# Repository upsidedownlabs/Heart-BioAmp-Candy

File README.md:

# Heart BioAmp Candy

[-white)](https://store.upsidedownlabs.tech/product/heart-bioamp-candy/)

Heart BioAmp Candy is a candy-sized sensor for recording ECG signals easily. It is perfect for students and researchers as it offers reliable and accurate ECG recordings, making heart monitoring accessible and convenient for educational and research purposes.

## Specifications

|Specs |      |
| ---- | ---- |
| Input Voltage | 2.7 V - 5 V |
| Fixed Gain | x2157 |
| Bandpass filter | 0.5 - 34 Hz |
| Compatible hardware | Any development board with an ADC (Arduino UNO R3/R4, Arduino Nano, Adafruit QtPy, STM32 Blue Pill, BeagleBone Black, Raspberry Pi Pico, to name just a few) or any standalone ADC of your choice |
| Biopotentials | ECG |
| No. of channels | 1 |
| Electrodes | 3 (Positive, Negative, and Reference) |
| Dimensions | 3.5 x 1.5 cm |
| Open-source | hardware + software |

## Hardware

Heart BioAmp Candy has been created using KiCad and all the design files can be found under [hardware](hardware/) folder, including [Interactive BOM](hardware/bom) file. Images below shows a quick overview of the hardware design.

## License

CERN Open Hardware License Version 2 - Strongly Reciprocal ([CERN-OHL-S-2.0](https://spdx.org/licenses/CERN-OHL-S-2.0.html)).

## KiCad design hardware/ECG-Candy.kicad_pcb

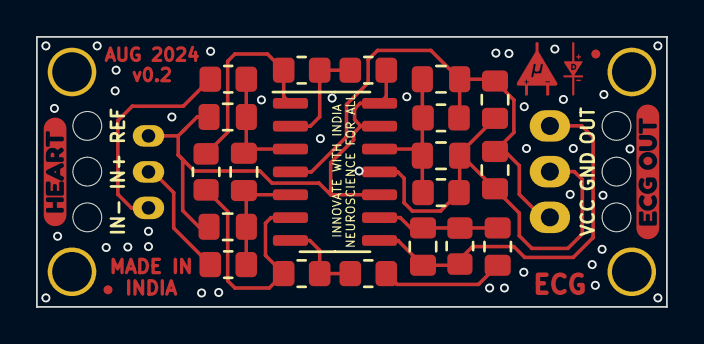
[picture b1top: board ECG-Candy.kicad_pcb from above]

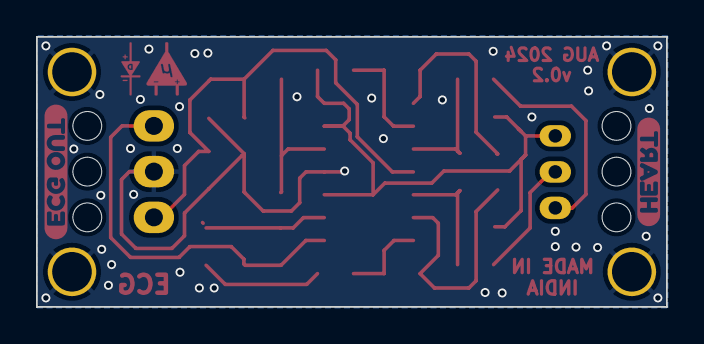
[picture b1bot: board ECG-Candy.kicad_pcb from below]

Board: 2 copper layers, 35.0 x 15.0 mm, 42 parts (10 on the bottom side), 13 nets.

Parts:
C1, C3: 100pF; C_0805_2012Metric_Pad1.18x1.45mm_HandSolder
C2, C5: 4.7nF; C_0805_2012Metric_Pad1.18x1.45mm_HandSolder
C4, C9: 100nF; C_0805_2012Metric_Pad1.18x1.45mm_HandSolder
C6: 47uF; C_0805_2012Metric_Pad1.18x1.45mm_HandSolder
C7, C10: 1uF; C_0805_2012Metric_Pad1.18x1.45mm_HandSolder
H1, H2, H3, H4, H5, H6, H7, H8, H9, H10: MountingHole; MountingHole_2.1mm
J1: IO; PinHeader_1x03_P2.54mm_Horizontal
J2: BioAmp_input; JST_PH_S3B-PH-K_1x03_P2.00mm_Horizontal
R1, R5: 22K; R_0805_2012Metric_Pad1.20x1.40mm_HandSolder
R2, R4: 220K; R_0805_2012Metric_Pad1.20x1.40mm_HandSolder
R3, R6, R10: 5.1K; R_0805_2012Metric_Pad1.20x1.40mm_HandSolder
R7, R8: 100K; R_0805_2012Metric_Pad1.20x1.40mm_HandSolder
R9: 1M; R_0805_2012Metric_Pad1.20x1.40mm_HandSolder
U1: Amp; SOIC-14_3.9x8.7mm_P1.27mm
kibuzzard-66A7D726: G***; kibuzzard-66A7D726
kibuzzard-66A7D805: G***; kibuzzard-66A7D805
kibuzzard-66AFEDBF: G***; kibuzzard-66AFEDBF
kibuzzard-66AFEDE1: G***; kibuzzard-66AFEDE1
kibuzzard-66AFEDEA: G***; kibuzzard-66AFEDEA
kibuzzard-66AFEDF0: G***; kibuzzard-66AFEDF0
kibuzzard-66AFEDFC: G***; kibuzzard-66AFEDFC
kibuzzard-66AFEE03: G***; kibuzzard-66AFEE03
kibuzzard-66AFEE09: G***; kibuzzard-66AFEE09
kibuzzard-66AFEE10: G***; kibuzzard-66AFEE10

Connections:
+5V: C4.2, C9.2, C10.1, R7.2, U1.4 (V+)
GND: C7.1, C9.1, C10.2, R8.1, U1.11 (V-)
unnamed: C6.1, R10.1
unnamed: R1.1, R5.2, U1.1
unnamed: R1.2, R4.1, U1.2 (-)
unnamed: R2.2, R5.1, U1.6 (-)
unnamed: C5.1, C6.2, R9.2, U1.9 (-)
unnamed: C4.1, C7.2, R7.1, R8.2, U1.12 (+)
ampRef: C1.2, C3.1, R4.2, U1.10 (+), U1.13 (-), U1.14
bpfOUT: C5.2, R9.1, U1.8
inaIN+: C2.1, C3.2, R6.1, U1.5 (+)
inaIN-: C1.1, C2.2, R3.1, U1.3 (+)
inaOUT: R2.1, R10.2, U1.7

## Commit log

2024-11-17 Add Heart BioAmp Candy v0.2 files
2024-11-18 Add Heart BioAmp Candy graphics
    Add edited images and connection diagram for Heart BioAmp Candy.
2024-11-19 Update README.md
    Update Heart BioAmp Candy images, add description, features, and connection diagram as well.
